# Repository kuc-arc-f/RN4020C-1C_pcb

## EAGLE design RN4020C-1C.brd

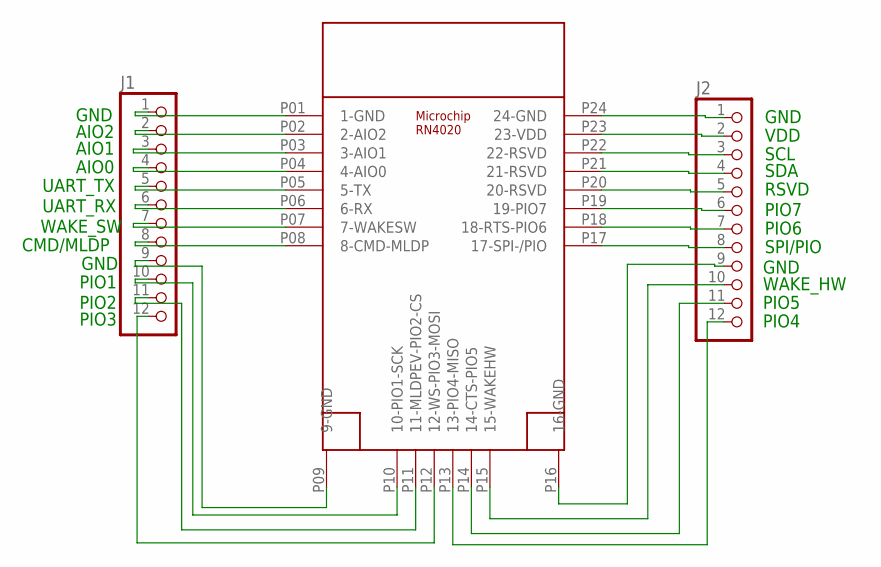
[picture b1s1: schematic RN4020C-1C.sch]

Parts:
J1, J2: PINHD-1X12; 1X12
U$2: RN4020; RN4020SMD

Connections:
unnamed: J1.1, U$2.P01 (1-GND)
unnamed: J1.2, U$2.P02 (2-AIO2)
unnamed: J1.3, U$2.P03 (3-AIO1)
unnamed: J1.4, U$2.P04 (4-AIO0)
unnamed: J1.5, U$2.P05 (5-TX)
unnamed: J1.6, U$2.P06 (6-RX)
unnamed: J1.7, U$2.P07 (7-WAKESW)
unnamed: J1.8, U$2.P08 (8-CMD-MLDP)
unnamed: J2.1, U$2.P24 (24-GND)
unnamed: J2.2, U$2.P23 (23-VDD)
unnamed: J2.3, U$2.P22 (22-RSVD)
unnamed: J2.4, U$2.P21 (21-RSVD)
unnamed: J2.5, U$2.P20 (20-RSVD)
unnamed: J2.6, U$2.P19 (19-PIO7)
unnamed: J2.7, U$2.P18 (18-RTS-PIO6)
unnamed: J2.8, U$2.P17 (17-SPI-/PIO)
unnamed: J1.9, U$2.P09 (9-GND)
unnamed: J1.10, U$2.P10 (10-PIO1-SCK)
unnamed: J1.11, U$2.P11 (11-MLDPEV-PIO2-CS)
unnamed: J1.12, U$2.P12 (12-WS-PIO3-MOSI)
unnamed: J2.9, U$2.P16 (16-GND)
unnamed: J2.10, U$2.P15 (15-WAKEHW)
unnamed: J2.11, U$2.P14 (14-CTS-PIO5)
unnamed: J2.12, U$2.P13 (13-PIO4-MISO)

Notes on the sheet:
GND
AIO2
AIO1
AIO0
UART_TX
UART_RX
WAKE_SW
CMD/MLDP
PIO1
PIO2
PIO3
VDD
SCL
SDA
RSVD
PIO7
PIO6
SPI/PIO
WAKE_HW
PIO5
PIO4

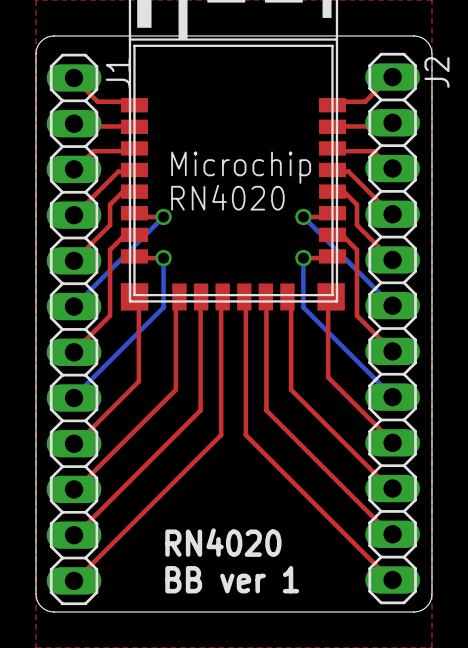
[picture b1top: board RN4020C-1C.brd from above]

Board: 2 copper layers, 22.0 x 32.0 mm, 3 parts (0 on the bottom side), 24 nets.

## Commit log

2017-12-09 new, 12-09A1
